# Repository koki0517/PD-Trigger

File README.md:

# PD-Trigger
出力がXT60なUSB PDトリガー

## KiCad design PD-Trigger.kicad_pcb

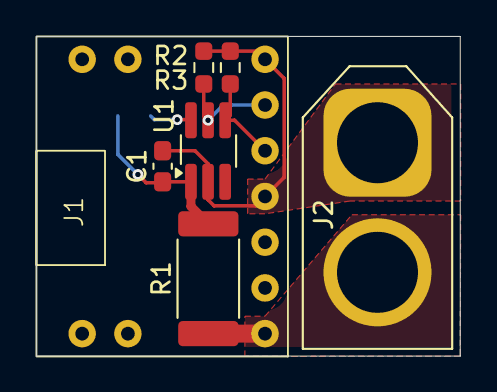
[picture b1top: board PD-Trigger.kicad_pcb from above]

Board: 2 copper layers, 23.5 x 17.8 mm, 8 parts (1 on the bottom side), 6 nets.

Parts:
C1: 1uF; C_0603_1608Metric_Pad1.08x0.95mm_HandSolder
J1: USB_DIP
J2: Conn_01x02; AMASS_XT60-M_1x02_P7.20mm_Vertical
R1: 1k; R_2512_6332Metric_Pad1.40x3.35mm_HandSolder
R2, R3: 5.1k; R_0603_1608Metric_Pad0.98x0.95mm_HandSolder
R_conf: 10k~200k; R_0603_1608Metric_Pad0.98x0.95mm_HandSolder
U1: TSOT-23-6_HandSoldering

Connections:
GND: C1.2, J1.4 (GND), J1.7 (GND), J2.1, R2.2, R3.2, U1.2 (GND)
unnamed: J1.5 (CC1), R2.1, U1.4 (CC1)
unnamed: J1.6 (CC2), R3.1, U1.5 (CC2)
unnamed: R_conf.1, U1.6 (CFG)
unnamed: C1.1, R1.2, R_conf.2, U1.1 (VDD)
VBUS: J1.1 (VBUS), J2.2, R1.1
